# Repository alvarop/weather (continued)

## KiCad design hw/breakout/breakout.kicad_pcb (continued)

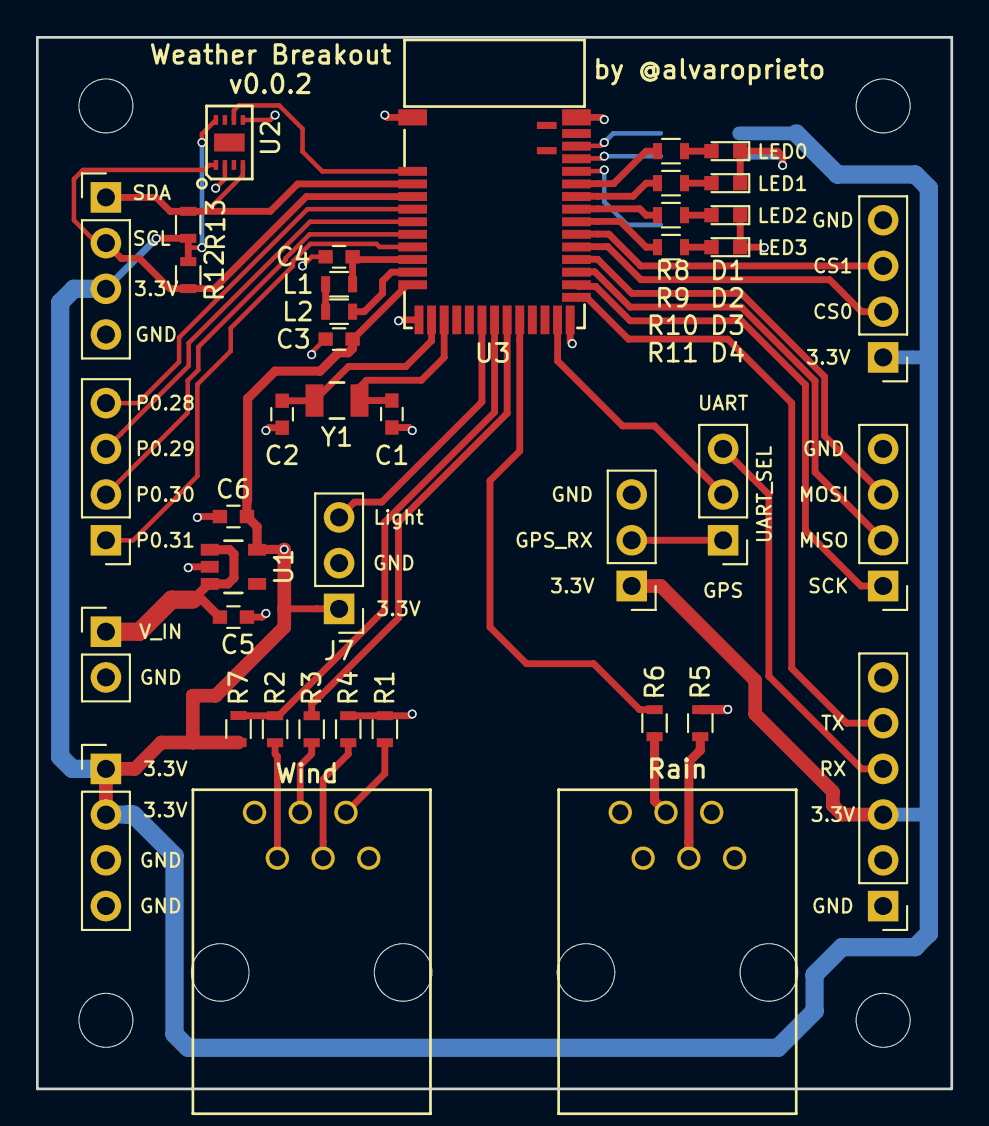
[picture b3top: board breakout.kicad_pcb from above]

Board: 2 copper layers, 50.8 x 58.4 mm, 42 parts (1 on the bottom side), 45 nets.

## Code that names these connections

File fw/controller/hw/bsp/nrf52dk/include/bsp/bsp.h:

/*
 * Licensed to the Apache Software Foundation (ASF) under one
 * or more contributor license agreements.  See the NOTICE file
 * distributed with this work for additional information
 * regarding copyright ownership.  The ASF licenses this file
 * to you under the Apache License, Version 2.0 (the
 * "License"); you may not use this file except in compliance
 * with the License.  You may obtain a copy of the License at
 *
 *  http://www.apache.org/licenses/LICENSE-2.0
 *
 * Unless required by applicable law or agreed to in writing,
 * software distributed under the License is distributed on an
 * "AS IS" BASIS, WITHOUT WARRANTIES OR CONDITIONS OF ANY
 * KIND, either express or implied.  See the License for the
 * specific language governing permissions and limitations
 * under the License.
 */

#ifndef H_BSP_H
#define H_BSP_H

#include <inttypes.h>

#include <syscfg/syscfg.h>

#ifdef __cplusplus
extern "C" {
#endif

/* Define special stackos sections */
#define sec_data_core   __attribute__((section(".data.core")))
#define sec_bss_core    __attribute__((section(".bss.core")))
#define sec_bss_nz_core __attribute__((section(".bss.core.nz")))

/* More convenient section placement macros. */
#define bssnz_t         sec_bss_nz_core

extern uint8_t _ram_start;
#define RAM_SIZE        0x10000

#define LED0           (20)
#define LED1           (19)
#define LED2           (18)
#define LED3           (17)
#define LED_BLINK_PIN   (LED0)

#define SPI_SCK (12)
#define SPI_MISO (13)
#define SPI_MOSI (14)
#define SPI_CS0 (16)
#define SPI_CS1 (15)

#define I2C_SDA (27)
#define I2C_SCL (26)

#define UART_TX (11)
#define UART_RX (10)

#define WX_WDIR (5)
#define WX_WDIR_AIN (3)
#define WX_WDIR_SAADC NRF_SAADC_INPUT_AIN3

#define WX_WSPEED (6)
#define WX_RAIN (7)

#define WX_LIGHT (4)
#define WX_LIGHT_AIN (2)
#define WX_LIGHT_SAADC NRF_SAADC_INPUT_AIN2

#ifdef __cplusplus
}
#endif

#endif  /* H_BSP_H */

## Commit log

2017-07-01 First commit - Adding mynewt blink fw files
2017-07-01 Added targets for nrf52
2017-07-01 Serial console seems to be working
2017-07-01 Adding wind/rain sensor driver (not done)
    Uses ADC to get wind direction for now
2017-07-01 Added windspeed measurement
2017-07-01 Adding basic rain sensor
2017-07-03 Trying to get I2C working
2017-07-06 Exposing probe command for i2c driver
2017-07-06 Whoops, fixed bad bug in i2c driver
2017-07-06 Adding simple sht3x driver
2017-07-06 Disabling AM2315 for now because I can't get it working :(
2017-09-30 Adding schematic for weather breakout board
2017-09-30 Finished breakout v0.0.1
2017-11-24 Added MPNs to breakout.sch
2017-11-24 Updated MDBT42Q footprint and layout
2017-11-24 Adding .gitignore
2018-01-07 Upgrading to mynewt 1.3.0
2018-01-07 Updating to work with weather breakout v0.0.1
2018-01-08 No more blinky!
2018-01-08 Switching BSP
2018-01-14 Update BSP for weather breakout v002
2018-01-14 Increase wind timer to 10 seconds and debounce rain sensor
2018-01-14 Update target to use new bsp
2018-01-15 Start updating adc driver so we can use multiple ones
2018-01-15 Moving my_drivers to drivers
    because it sounds funny
2018-01-15 gnu99 instead of c99
2018-01-15 Adding TEMT6000 driver
2018-01-15 Start using pins from BSP
2018-01-15 Add syscfg values for sensor poll times
2018-01-15 Removed shell
2018-01-16 Update version on schematic
2018-01-16 Updating repos
2018-01-16 Enabling BMP280 driver!
2018-01-16 Adding pipenv stuff
2018-01-16 Adding BGLib
2018-01-16 Stop tracking repos/ in git
2018-01-16 Add initial BLE advertising option
    Only pressure and temperature are available at the moment
2018-01-17 Enable timestamp and only advertise every SAMPLE_PERIOD_S
2018-01-17 Adding simple BLE scanner to decode weather beacon packets
    To run use:
    pipenv run sw/scripts/simple_scan.py --port /dev/ttyACM0
2018-01-17 Update windrain and light sensors to be polled and update beacon
2018-01-20 Updating beacon and decoder
2018-01-21 Adding basic csv plotter
2018-01-22 Adding ignored_fields instead of manually checking for them
2018-10-03 Starting nucleo weather breakout
2018-10-04 Released nucleo weather breakout v0.1 to kicad
2018-12-23 Starting work on PCB updates
2018-12-23 Layout pretty much done. Time to review!
2018-12-29 Updated part numbers
2018-12-29 Released to JLCPCB
2018-12-29 Fixed wiring bugs from design
    GPS_FIX line was shared with uart, so moved
    WSPEED and WDIR pinout was flipped in new connector
    RAIN unnaffected since it's just a reed switch
2019-01-03 Chaac schematic almost done :D
2019-01-03 Began placement for chaac
2019-01-04 Removed GPS, re-did placement
2019-01-04 Finished chaac 1.0 schematic and layout
    Released to JLCPCB
